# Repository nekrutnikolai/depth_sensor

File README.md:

## Low-Cost Depth Sensing Module For Deep-Water Instruments

<p align="center">
  AI-generated image of a depth sensor
</p>

<p align="center">
  Or here's what the current prototype will look like
</p>

A low-cost, durable depth-sensing module capable of providing approximate depth readings for underwater instruments submerged up to 2000 meters. Deliverables will include a fully functional prototype, field-tested for real-world integration.

> in Partial Fulfillment of the Requirements for the Degree of Master of Engineering, Electrical and Computer Engineering at Cornell University

### Introduction

This project addresses the challenge of developing a cost-effective depth sensor for intermediate to deep depths (up to 2000 meters). Existing solutions are either prohibitively expensive or unsuitable for these depths. In collaboration with Dr. V. Hunter Adams (Cornell ECE) and Jonathan Pfeifer (WHOI), this effort focuses on creating a robust, affordable sensor module designed for integration with underwater exploration vessels. The sensor balances practical accuracy with resilience to high-pressure underwater environments, supporting WHOI’s marine research with an innovative and accessible solution.

### Updates

> Recent on top and older on bottom

#### Potential epoxy options

> Mar 2025

We need ~ 100ml of epoxy to encapsulate electronics and custom break out Pi Pico.

#### Calculating number of hall effect sensors

> Feb 2025

The specification is to be able to work across the 2000m range with a resolution of +/- 10m. 

Thus, the minimum resultion we need to have is 2000m / 10m = 200 points.

From [this article](https://pico-adc.markomo.me/ENOB/), the effective bits of the Pi Pico ADC is approximatle **8.8 bits**.

With a conservative estimate, this is around 2 ^ 8.8 ~ 400 discrete values not affected by noise internal to the ADC

As we can see, even having one hall effect sensor would be enough and would get us to within 5m resolution. 

Since there are three ADCs available on the Pi Pico and the Hall Effect sensors are quite inexpensive, why not utilize three three hall effect sensors for approximately a 3 * 400 ~ 1200 point resolution. For the range of 2000m, this leads to a precision of about 1.67m.

Going beyond that has little benefit

#### Acquiring and plotting live ADC data

> Jan 2025

Wrote program to output ADC data over serial and to a real-time plotter program on my computer where I was measuring the voltage from a potentiometer. This program will serve as a good way to characterize the future hall-effect sensors.

<p align="center">
  Live plot of ADC plotter
</p>

<p align="center">
  Breadboard setup of potentiometer
</p>

#### Initial PCB design

> Nov 2024

Designed PCB schematic found in /depth_sensor_KiCad as per image below:

<p align="center">
  Image of schematic
</p>

#### Exploring physical mechanisms with which to measure pressure

> Oct 2024

Compressible fluids research: https://hackmd.io/@nekrutnikolai/rJiTfUMA0

We decided to initially move forward with an approach that utilizes the linear compressibility of liquids, such as sea water, under high pressure. These linearly compressible liquids, such as water or ethanol exhibit an interesting property where their change in volume is linear with respect to pressure rather than a 1/x relationship. The change in volume at a depth of 2000m, which is a pressure of 200 atm is approximately 1% less than atmospheric volume. The prototype will work by having a piston composed of a magnet that moves as the fluid is compressed more and more at greater depths. The position of the magnet is to be determined precisely by using a linear array of hall effect sensors as this is a non-invaise way to measure the position of the magnet.

<!-- Components have arrived but turns out that I received the wrong ones: -->

### Specifications to Meet

| **Parameter**      | **Specification**               |
|---------------------|---------------------------------|
| **Depth**          | 2,000 m                         |
| **Pressure**       | 200 atm                         |
| **Power Input**    | 5-24V @ ≤ 100mA                 |
| **Data Protocol**  | RS-232                          |
| **Physical Size**  | Soda can - Nalgene bottle sized |
| **Connector Type** | MacArtney SubConn               |
| **Accuracy**       | ±10 m                           |
| **Mounting**       | Hose clamps, bolts, etc.        |

### Timeline  
This project spans two semesters: **FA 2024 - SP 2025** with the following timeline:  

#### Fall 2024 Semester  
- ✅ **Sep-Nov**: Conduct research and finalize physical sensing mechanism  
- ✅ **Nov**: Order components  
- ⬜ **Dec**: Design circuit PCB (in progress)  
- ⬜ **Dec**: Initial testing with ordered components (in progress)  

#### Spring 2025 Semester  
- ⬜ **Jan-Feb**: Design algorithm to translate physical system into depth readings  
- ⬜ **Jan-Feb**: Assemble prototype & test at Helen Newman Pool  
- ⬜ **Feb**: Complete interface design and implement energy-efficient adjustments  
- ⬜ **Feb-Mar**: Integrate final hardware and software, prepare for field testing  
- ⬜ **Mar-Apr**: Perform field testing with WHOI; collect data and refine design  
- ⬜ **May**: Finalize module, complete documentation, and hand over the prototype to WHOI

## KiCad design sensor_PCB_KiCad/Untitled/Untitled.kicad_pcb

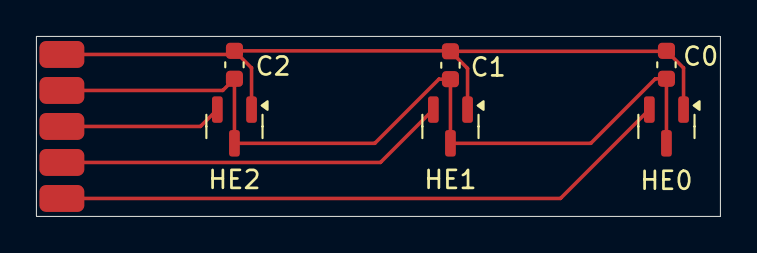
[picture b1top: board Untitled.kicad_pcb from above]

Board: 2 copper layers, 38.0 x 10.0 mm, 7 parts (0 on the bottom side), 5 nets.

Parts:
C0, C1, C2: 0.01u; C_0603_1608Metric
HE0: ADC 0; SOT-23
HE1: ADC 1; SOT-23
HE2: ADC 2; SOT-23
U4: PCB_HallEffect

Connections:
+3V3: C0.1, C1.1, C2.1, HE0.1 (VCC), HE1.1 (VCC), HE2.1 (VCC), U4.1 (Vcc)
GND: C0.2, C1.2, C2.2, HE0.3 (GND), HE1.3 (GND), HE2.3 (GND), U4.2 (Gnd)
unnamed: HE0.2 (OUT), U4.5 (ADC_3)
unnamed: HE1.2 (OUT), U4.4 (ADC_2)
unnamed: HE2.2 (OUT), U4.3 (ADC_1)

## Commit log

2024-11-29 plotted PCB v1
2025-01-26 working on readme
2025-01-26 added a readme tag
2025-01-26 fixed typo
2025-01-27 revamped README
2025-01-27 adding image
2025-01-27 centered text
2025-02-09 progress update
2025-02-09 updated gitignore
2025-02-09 extended readme
2025-02-09 fixed typos
2025-02-09 worked on sensor code
2025-02-10 added image
2025-02-24 added updates to readme
2025-02-24 edited dimensions file
2025-04-24 added code
2025-04-26 started working on data analysis script
2025-04-27 added .csv files
2025-04-30 added more data
2025-05-01 did more data analysis
2025-05-16 added latest changes
